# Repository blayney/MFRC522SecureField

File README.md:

# MFRC522SecureField
A secure RFID system via MFRC522 and CE40HX1K-TQ144 FPGA.

The this repo is to track changes made to the hardware, and view issues for each version of the hardware independently.
This means that if a change is made to layout or to firmware / FPGA layout, and it causes a hardware issue, we can trace it back to the PR.

All layout and schema design is done in KiCad v5 and includes custom made libraries for new symbols and their footprints.

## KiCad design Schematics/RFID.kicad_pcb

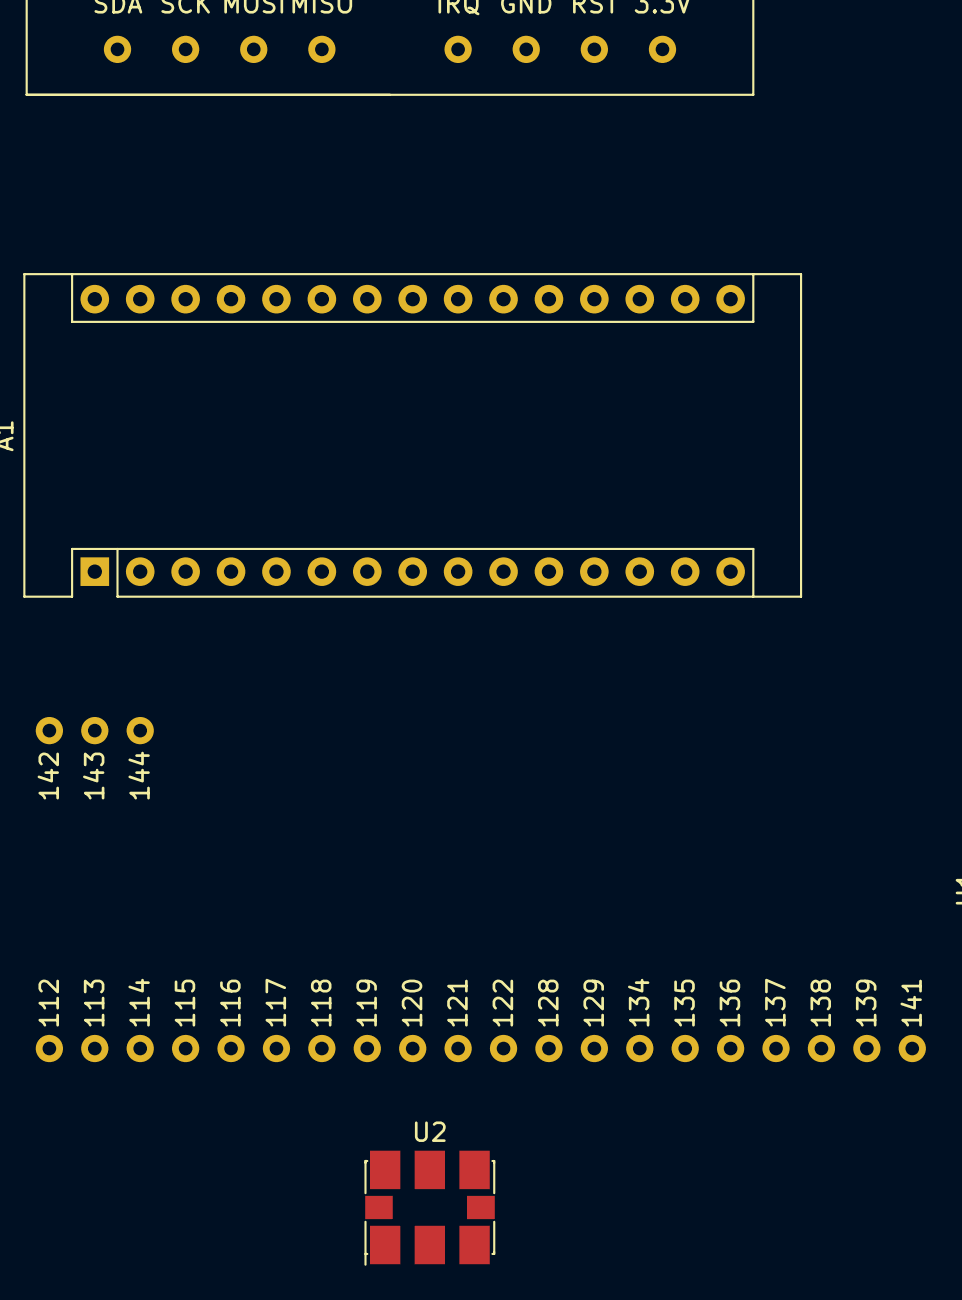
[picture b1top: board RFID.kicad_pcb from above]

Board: 2 copper layers, 4 parts (0 on the bottom side), 7 nets, no tracks yet.

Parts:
A1: Arduino_Nano_v3.x; Arduino_Nano
P1: RFID-RC522-MODULE; RFID-RC522
U1: ICE40HX1K-TQ144; ICE40-CM
U2: NA555; Oscillator_SMD_SI570_SI571_Standard

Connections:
unnamed: A1.3, P1.7
unnamed: A1.13, P1.1
unnamed: A1.14, P1.3
unnamed: A1.15, P1.4
unnamed: A1.16, P1.2
unnamed: A1.17, P1.8
unnamed: A1.27, A1.29, P1.6, U2.1, U2.2, U2.4, U2.5

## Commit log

2020-04-07 Init
2020-04-07 Added Layout and Schemas
2020-04-07 Added RMMD
2020-04-07 Updated RMMD
2020-05-17 Added custom sketches
